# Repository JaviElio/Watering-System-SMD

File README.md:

# Watering-System-SMD

Watering system with Attiny84 and i2c moisture sensor.

THINGSPEAK LINK:

https://thingspeak.com/channels/339098

FEATURES:

 - Measures soil moisture, light and temperature.
 - It waters only at night.
 - It doesn't water if temperature is below 4ºC.
 - It waters depending on a preset value and a hysteresis.

 - It takes measurements every hour, then microcontroller goes to deep sleep.
 - If it irrigates, then checks moisture again after five minutes.
 - Measurements are uploaded to thingspeak.com

BILL OF MATERIALS:

 - Valve: https://www.aliexpress.com/item/Free-shipping-Plastic-solenoid-valve-12VDC-for-drink-water-air-6-35mm-1-4-Quick-plug/1411672083.html?spm=2114.13010608.0.0.Ew7MCd
 
 - I2C Soil moisture sensor: https://www.tindie.com/products/miceuz/i2c-soil-moisture-sensor/?pt=full_prod_search
 
 - Enclosure: https://www.aliexpress.com/item/New-1-PC-Waterproof-115x90x55MM-Cover-Plastic-Electronic-Project-Box-Enclosure-Case-VE837-P0-3/32701644399.html?spm=2114.13010608.0.0.FBugqX
 
 - Attiny84
 - MCP1703
 - 2N7000
 - AO3400
 - ESP-01

**TO IMPROVE**
 - Change protection diode with a schottky diode
 - Add a resistor in serial with diode D2 to close the EV slower
 - Connect the electrovalve and the diode D2 after the diode protection diode.

**PICTURES:**

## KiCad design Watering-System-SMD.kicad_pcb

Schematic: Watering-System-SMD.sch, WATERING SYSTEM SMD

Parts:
C1, C2: 1uF; C_0805_HandSoldering
C3: 0.1uF; C_0805_HandSoldering
CON1: AVR-ISP-6; Pin_Header_Straight_2x03_Pitch2.54mm
D1, D2: M7; D_SMA_Handsoldering
J1: Screw_Terminal_1x02; TerminalBlock_Pheonix_MKDS1.5-2pol
J2: CONN_01X04_MALE; Pin_Header_Straight_1x04_Pitch2.54mm
J3: Screw_Terminal_1x04; TerminalBlock_Pheonix_MPT-2.54mm_4pol
J4: Screw_Terminal_1x02; TerminalBlock_Pheonix_MPT-2.54mm_2pol
Q1: AO3400; SOT-23
Q2: 2N7002; SOT-23
R1, R2: 4k7; R_0805_HandSoldering
R3, R4: 10k; R_0805_HandSoldering
R5, R6: 330; R_0805_HandSoldering
U1: MCP1703A-3302/MB; SOT-89-3_Handsoldering
U2: ATTINY84-20SSU; SOIC-14_N
U3: ESP-01

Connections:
+12V: D1.2 (A), D2.1 (K), J1.2, J4.2
/CH_PD: U2.6 ((PCINT7/ICP/OC0B/ADC7)PA7), U3.6 (~CH_PD)
/EV_CONN: D2.2 (A), J4.1, Q1.3
/EV_ON: CON1.1, R3.2, R5.2, U2.8 ((PCINT5/DO/MISO/OC1B/ADC5)PA5)
/RST: CON1.5, U2.4 ((PCINT11/dW/~RESET~)PB3)
/RX: J2.3, U2.11 ((PCINT2/AIN1/ADC2)PA2), U3.4 (RXD)
/SCL: CON1.3, J2.1, J3.2, R2.1, U2.9 ((PCINT4/USCK/SCL/T1/ADC4)PA4)
/SDA: CON1.4, J2.2, J3.1, R1.1, U2.7 ((PCINT6/SDA/DI/MOSI/OC1A/ADC6)PA6)
/SENSOR_CONN: J3.3, Q2.3 (D)
/SENSOR_ON: R4.2, R6.2, U2.2 ((PCINT8/CLKI/XTAL1)PB0)
/TX: J2.4, U2.10 ((PCINT3/T0/ADC3)PA3), U3.5 (TXD)
GND: C1.2, C2.2, C3.2, CON1.6, J1.1, Q1.2, Q2.2 (S), R3.1, R4.1, U1.1 (GND), U2.14 (GND), U3.1 (GND)
unnamed: C1.1, D1.1 (K), U1.2 (VI)
unnamed: Q1.1, R5.1
unnamed: Q2.1 (G), R6.1
VCC: C2.1, C3.1, CON1.2, J3.4, R1.2, R2.2, U1.3 (VO), U2.1 (VCC), U3.7 (~RST), U3.8 (VCC)

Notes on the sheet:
V. Regulator
Connections
I2C
WIFI
Transistors

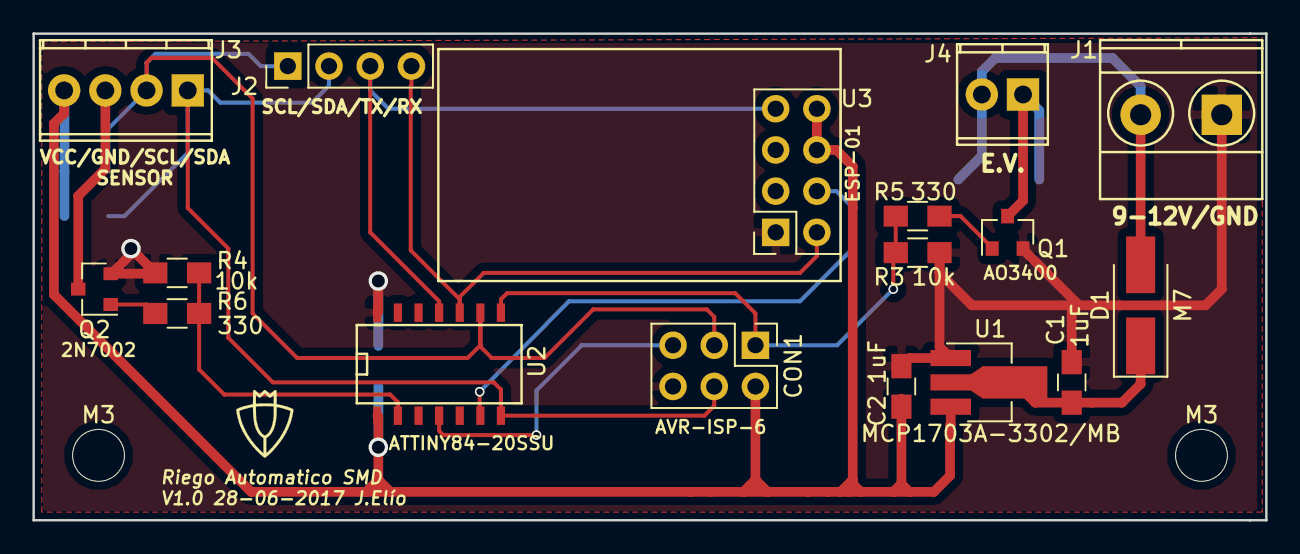
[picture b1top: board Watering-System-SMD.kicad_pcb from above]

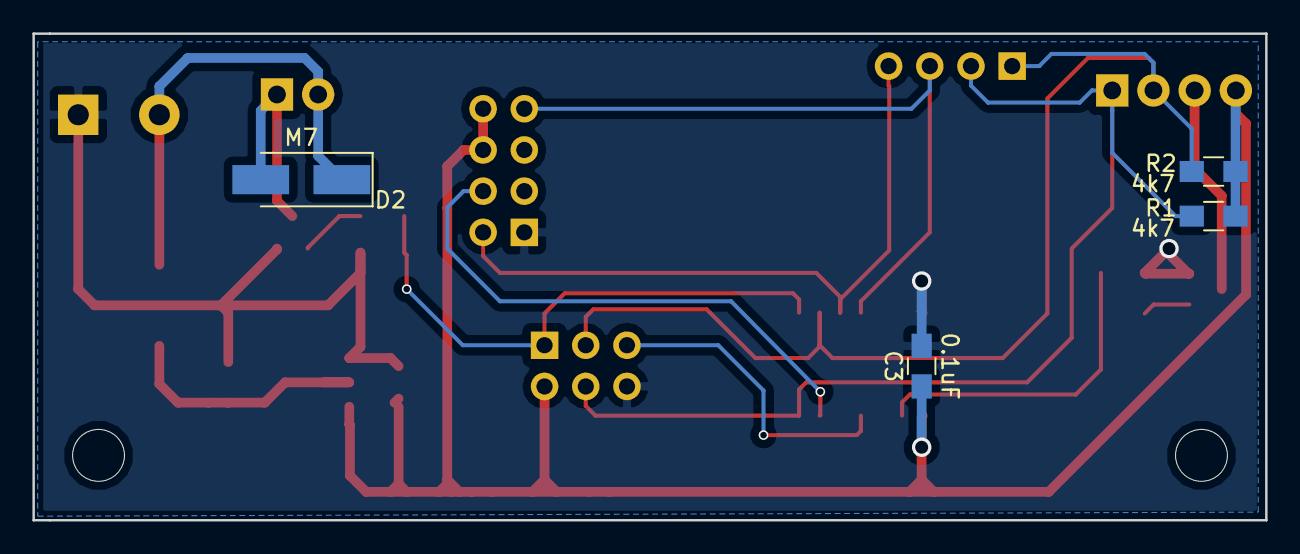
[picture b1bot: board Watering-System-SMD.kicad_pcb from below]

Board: 2 copper layers, 76.0 x 30.0 mm, 23 parts (4 on the bottom side), 16 nets.

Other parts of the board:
M3, M3#2: MountingHole_3.2mm_M3

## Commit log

2017-05-22 Initial upload
2017-06-15 ESP-01 added
2017-06-17 PCB routed
2017-06-17 SilkScreen changed
2017-06-19 gerber folder uploaded
2017-06-20 logo added to silkscreen
2017-06-28 CH-PD routed
2017-06-28 date changed
2017-06-28 gerbers uploaded
2017-07-29 Pictures added
2017-08-09 PDF uploaded
2017-08-18 Some tests
2017-08-26 uController send data to ESP8266 and then it is uploaded to Thingspeak.
2017-08-26 Readmed.md changed
2017-08-27 Document uploaded
2017-08-27 First working version. It measure temperature, moisture, and light. Waters depending on this measurements and then sleeps.
2017-10-18 MOSFET transistor changed
2017-10-18 MOSFET changed
2017-10-18 README changed
2017-10-27 README.md changed
2017-10-27 minor changes
2017-10-27 thingspeak link added
